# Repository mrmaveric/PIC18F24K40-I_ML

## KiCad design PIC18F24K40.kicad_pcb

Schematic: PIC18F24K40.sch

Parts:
C1, C4, C5: 0.1uf; C_0603_1608Metric_Pad1.05x0.95mm_HandSolder
C2, C3: 47pf; C_0603_1608Metric_Pad1.05x0.95mm_HandSolder
C6: 0.01uf; C_0603_1608Metric_Pad1.05x0.95mm_HandSolder
D1: blue; LED_0603_1608Metric; Manufacturer Part Number 19-213SUBC/S400-A5/S208-2/TR8
FB1: 330 Ohms @ 100MHz; C_0603_1608Metric_Pad1.05x0.95mm_HandSolder; Manufacturer Part Number BLM18SG331TN1D
J1, J2: Conn_01x13; PinHeader_1x13_P2.54mm_Vertical; Manufacturer Part Number PREC013SAAN-RC
J3: ICSP; PinHeader_1x06_P2.54mm_Vertical; Manufacturer Part Number PREC006SABN-RC
J4: USB_B_Micro; USB_Micro-B_Molex_47346-0001; Manufacturer Part Number 0473460001
Q1: Q_Photo_NPN; LED_0603_1608Metric; Manufacturer Part Number PT19-21B/L41/TR8
R1, R2: 27; R_0603_1608Metric_Pad1.05x0.95mm_HandSolder
R3, R5: 10k; R_0603_1608Metric_Pad1.05x0.95mm_HandSolder
R4: 360; R_0603_1608Metric_Pad1.05x0.95mm_HandSolder
SW1: SW_SPST; SW_SPST_B3U-1000P; Manufacturer Part Number B3U-1000P
U1: FT231XQ; QFN-20-1EP_4x4mm_P0.5mm_EP2.5x2.5mm; Manufacturer Part Number FT231XQ-R
U2: PIC18F24K40-I_ML; QFN-28-1EP_6x6mm_P0.65mm_EP4.25x4.25mm; Manufacturer Part Number PIC18F24K40T-I/ML

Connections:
/RA0: J1.1, U2.27 (RA0)
/RA1: J1.2, U2.28 (RA1)
/RA2: J1.3, U2.1 (RA2)
/RA3: J1.4, U2.2 (RA3)
/RA4: J1.5, U2.3 (RA4)
/RA5: J1.6, U2.4 (RA5)
/RA6: J1.7, U2.6 (RA7)
/RA7: J1.8, U2.7 (RA6)
/RB0: J2.10, U2.18 (RB0)
/RB1: J2.9, U2.19 (RB1)
/RB2: J2.8, U2.20 (RB2)
/RB3: J2.7, U2.21 (RB3)
/RB4: J2.6, U2.22 (RB4)
/RB5: J2.5, U2.23 (RB5)
/RB6: J2.4, J3.5 (ICSPCLK), U2.24 (RB6/ICSPCLK)
/RB7: J2.3, J3.4 (ICSPDAT), U2.25 (RB7/ICSPDAT)
/RC0: J1.9, U2.8 (RC0)
/RC1: J1.10, U2.9 (RC1)
/RC2: J1.11, U2.10 (RC2)
/RC3: J1.12, U2.11 (RC3)
/RC4: D1.2, J1.13, U2.12 (RC4)
/RC5: C6.1, J2.13, Q1.1, R5.1, U2.13 (RC5)
/RC6: J2.12, U1.1, U2.14 (RC6)
/RC7: J2.11, U1.17, U2.15 (RC7)
/RE3: C5.1, J3.1 (~MCLR), R3.2, SW1.2, U2.26 (RE3_~MCLR)
GND: C1.2, C2.2, C3.2, C4.2, C6.2, J2.2, J3.3 (VSS), J4.5, J4.6, Q1.2, R4.2, SW1.1, U1.3, U1.13, U1.21, U2.5 (VSS), U2.16 (VSS)
unnamed: C2.1, J4.2, R1.2
unnamed: C3.1, J4.3, R2.2
unnamed: C4.1, U1.10, U1.11, U1.20
unnamed: C5.2, U1.18
unnamed: D1.1, R4.1
unnamed: FB1.2, J4.1
unnamed: R1.1, U1.9
unnamed: R2.1, U1.8
VCC: C1.1, FB1.1, J2.1, J3.2 (VDD), R3.1, R5.2, U1.12, U2.17 (VDD)

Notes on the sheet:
RX1
TX1
PICKIT programmer headder
PIC18F24K40
Alternate part number for female header: PPTC131LFBN-RC
Alternate part number for right angle PRPC006SBAN-M71RC

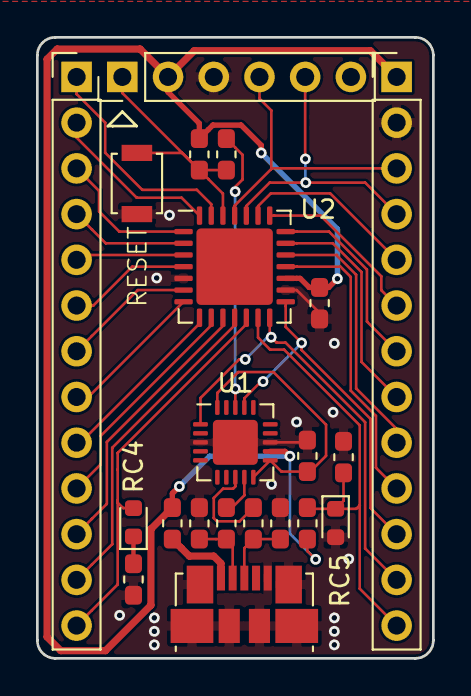
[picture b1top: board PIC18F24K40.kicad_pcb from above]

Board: 2 copper layers, 22.0 x 34.5 mm, 21 parts (0 on the bottom side), 35 nets.

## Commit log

2018-10-23 Project created
    This project is an evaluation board for the PIC18F24K40
    microcontroller
    It will contain:
    - a PIC18F24K40-I/ML QFN
    - a usb connector
    - a usb FTDI chip
2018-10-23 Components added to schlib
    - voltage regulator added
    - PIC18F24K40-I_ML added
2018-10-23 Progressing through kicad setup
    PCBLIB:
    - QFN package for PIC added
    SCH:
    - Voltage regulator circuit placed
    - Package pinout image placed
    - PIC placed
2018-10-23 test board layout
    I think I may want to drop the regulator
2018-10-23 Regulator removed
2018-10-23 Added datasheet for potential FTDI chip
2018-10-24 adding .gitignore file to clean up repo
2018-10-24 Mostly cleanup
    Backup and cache files are no longer versioned.
    I've changed the breakout headers to 13 pin from 14 as we don't need
    multiple power and ground pins broken out.
    I think this board will be much more useful if it has the ability to
    talk to a computer, so I'll be adding a part for the FTDI chip in the
    reference folder, along with a USB type ? connector.
2018-10-24 Basic layout and schematic capture
    SCH:
    - added decoupling cap for micro
    PCB:
    - fill on top layer removed
    - decoupling cap placed next to micro
    MODEL:
2018-10-24 ICSP header pin 1 visability
2018-10-24 Added a reference datasheet for a cute button
    I think I might add a couple of these as input for the board along with
    a small pot and a couple of leds for output
2018-10-24 USB and FTDI circuit added
    I've added a datasheet for usb micro connector I plan on using.
    SCH:
    - USB and FTDI placed with supporting passives
    PCB:
    - Initial layout of USB micro and FTDI chip done
2018-10-24 Cleaning up the repo
2018-10-24 Added some outputs
    So progress can be viewed without the tool
2018-10-25 Initial route complete
    This may be the design I get prototyped, unless I can think of anything
    I would like to change in the next few days.
    Outputs updated so the files can be viewed without kicad. Fab outputs
    will be generated and commited when I get the prototypes fabbed.
2018-10-25 Thickened up VCC track to micro
    I accidently routed the power to the micro at data trace width. Woops
2018-10-25 Updated render to show traces
    Original render didn't show the traces and my vanity couln't take it.
2018-10-25 Logo added; fab outputs generated
    I've added a test logo to the back silkscreen to see how the
    manufacturer does.
2018-10-26 Ordering information added to schematic elements
    Manufacturer and part number added.
2018-10-26 Option for using sockets
    Part numbers and models for female connections added
2018-10-26 Reset button added Designators hidden
2018-10-26 Renders and fab outputs updated
2018-10-26 Ordering details added for push button
2018-10-26 PCB corners rounded to look pretty
2018-10-28 LED and phototransistor added
    I've added an LED for output and phototransistor for input. No button
    though.
2018-10-28 Labels added to LED/Photo transistor
2018-10-29 Board sent to printer JLCPCB-W20181029138130
2018-10-31 RC5 now connected to the right place
    OMG I screwed up the light sensor connection! The boards come in soon...
    Schematic and board updated. Will kynar the prototypes
